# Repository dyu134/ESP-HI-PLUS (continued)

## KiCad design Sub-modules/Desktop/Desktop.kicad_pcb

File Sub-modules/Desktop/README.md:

# Desktop Sub-module

The **Desktop** sub-module is an environment-sensing and time-keeping expansion board for the **ESP-HI-PLUS**. It transforms the voice assistant into a desktop companion capable of monitoring room conditions and detecting human presence.

## Features

### Core Compute

- **RP2040** (U3) — Dual-core ARM Cortex-M0+ microcontroller to handle local sensor processing and timing.
- **16 Mbit Flash** (U1) — Storage for RP2040 firmware.

### Environment Sensors

- **SHT4x** (U5) — High-accuracy relative humidity and temperature sensor.
- **STHS34PF80** (U6) — Infrared sensor for presence and motion detection.
- **VEML7700** (U7) — Ambient light sensor for automatic display brightness adjustment.

### Time Keeping

- **MCP79410** (U8) — I²C Real-Time Clock with SRAM and battery backup.
- **CR2032 Battery** (BT1) — Ensures the clock keeps time even when the main board is powered off.

### Identification & Metadata

The Desktop module follows the standard [ESP-HI-PLUS identification protocol](../README.md).

- **R_ID (383 kΩ)** — Identifies the module as **Class 3 (Sensor — Environmental)**.
- **AT24CS02** (U10) — 2 Kbit I²C EEPROM carrying module metadata and serial number.

#### EEPROM Metadata

| Offset | Size | Field | Value (Hex) | Value (Decoded) | Description |
| :------: | :----: | :------ | :-----------: | :---------------- | :------------ |
| 0x00 | 4 | Magic Number | 45 53 50 4D | "ESPM" | ASCII sanity check |
| 0x04 | 1 | Class ID | 0x03 | 3 | Sensor - Environmental |
| 0x05 | 1 | Module ID | 0x01 | 1 | Desktop v1.17 |
| 0x06 | 1 | HW Revision | 0x01 | 1 | First PCB revision |
| 0x07 | 2 | FW Revision | 0x1101 | 1.17 | Major.Minor |
| 0x09 | 1 | Protocol Revision | 0x01 | 1 | Communication protocol v1 |
| 0x0A | 1 | Power Requirement | 0x00 | Self-powered | USB-C powered, no V_BUS needed |
| 0x0B | 2 | Max Current (mA) | 0x01F4 | 500 mA | Maximum draw (little-endian) |
| 0x0D | 2 | Min Voltage (mV) | 0x1194 | 4500 mV | Minimum supply voltage (little-endian) |
| 0x0F | 2 | Boot Delay (ms) | 0x0064 | 100 ms | Power-on delay (little-endian) |
| 0x11 | 4 | Capability Bitmask | 0x0000000D | — | Bits 0, 2, 3 enabled (see below) |
| 0x15 | 16 | Module Name | 44 65 73 6B... | "Desktop" | ASCII, null-terminated |
| 0x25 | 16 | Serial Number | 44 43 2D 30... | "DC-001-ABCD" | ASCII, null-terminated |
| 0x35 | 198 | User Data | — | — | Available for custom data |
| 0xFB | 4 | CRC32 | 0xXXXXXXXX | — | CRC32 of bytes 0x00–0xFA |

#### Capability Bitmask

**Value:** `0x0000000D` (Bits 0, 2, and 3 set)

| Bit | Value | Capability | Status |
| :---: | :---: | :--- | :--- |
| 0 | 0x01 | Needs Calibration | ✅ Enabled |
| 1 | 0x02 | Requires ACK | ❌ Disabled |
| 2 | 0x04 | Async Data | ✅ Enabled |
| 3 | 0x08 | Supports Sleep | ✅ Enabled |
| 4 | 0x10 | Has Emergency Stop | ❌ Disabled |
| 5 | 0x20 | Supports OTA | ❌ Disabled |
| 6 | 0x40 | Has Battery Backup | ❌ Disabled |
| 7 | 0x80 | Requires Bootloader Mode | ❌ Disabled |
| 8–31 | — | Reserved | — |

### User Interface & IO

- **WS2812B-2020** (D2) — Addressable RGB LED for status or mood lighting.
- **Tactile Switches** (SW1, SW3) — Reset and bootmode selection switching.
- **Snooze Button** (SW2) — **Kailh MX mechanical keyboard switch** (hotswap) for sleep mode activation.
- **USB-C Port** (J1) — For independent programming and powering of the RP2040.

## Integration

This module identifies itself as an environmental sensor class. The ESP-HI-PLUS main board can read data from the onboard sensors through commands to the RP2040 via UART through the magnetic pogo-pin connectors.

### Pinouts (Magnetic Pogo Connectors)

The Desktop module uses two 5-pin magnetic pogo-pin connectors to interface with the main board.

#### J2 (MAG1)

| Pin | Name   | Description                                           |
| --- | ------ | ----------------------------------------------------- |
| 1   | VMAIN  | 2-way power bus shared with main module               |
| 2   | GND    | Ground                                                |
| 3   | UART RX| From main module for data transmission                |
| 4   | UART TX| From main module for data transmission                |
| 5   | EN     | Main module control to enable/disable submodule power |

#### J3 (MAG2)

| Pin | Name     | Description                                     |
| --- | -------- | ----------------------------------------------- |
| 1   | I2C SDA  | For reading module ID metadata EEPROM           |
| 2   | I2C SCL  | For reading module ID metadata EEPROM           |
| 3   | AUX1/ID0 | Hardware class identifier resistor              |
| 4   | AUX2     | Auxiliary data pin (unused)                     |
| 5   | AUX3     | Auxiliary data pin (unused)                     |

## Repository Layout

```text
.
├── Desktop.kicad_pro           # KiCad project file
├── Desktop.kicad_sch           # Schematic
├── Desktop.kicad_pcb           # PCB layout
├── Desktop Symbols/            # Project-local schematic symbols
├── Desktop Footprints/         # Project-local footprint libraries
├── Desktop 3D Models/          # STEP models
└── production/                 # Manufacturing outputs
    ├── bom.csv                 # Bill of materials
    └── ESP-HI-PLUS_Desktop_Sub-module_v1.17.zip # Production archive (latest)
```

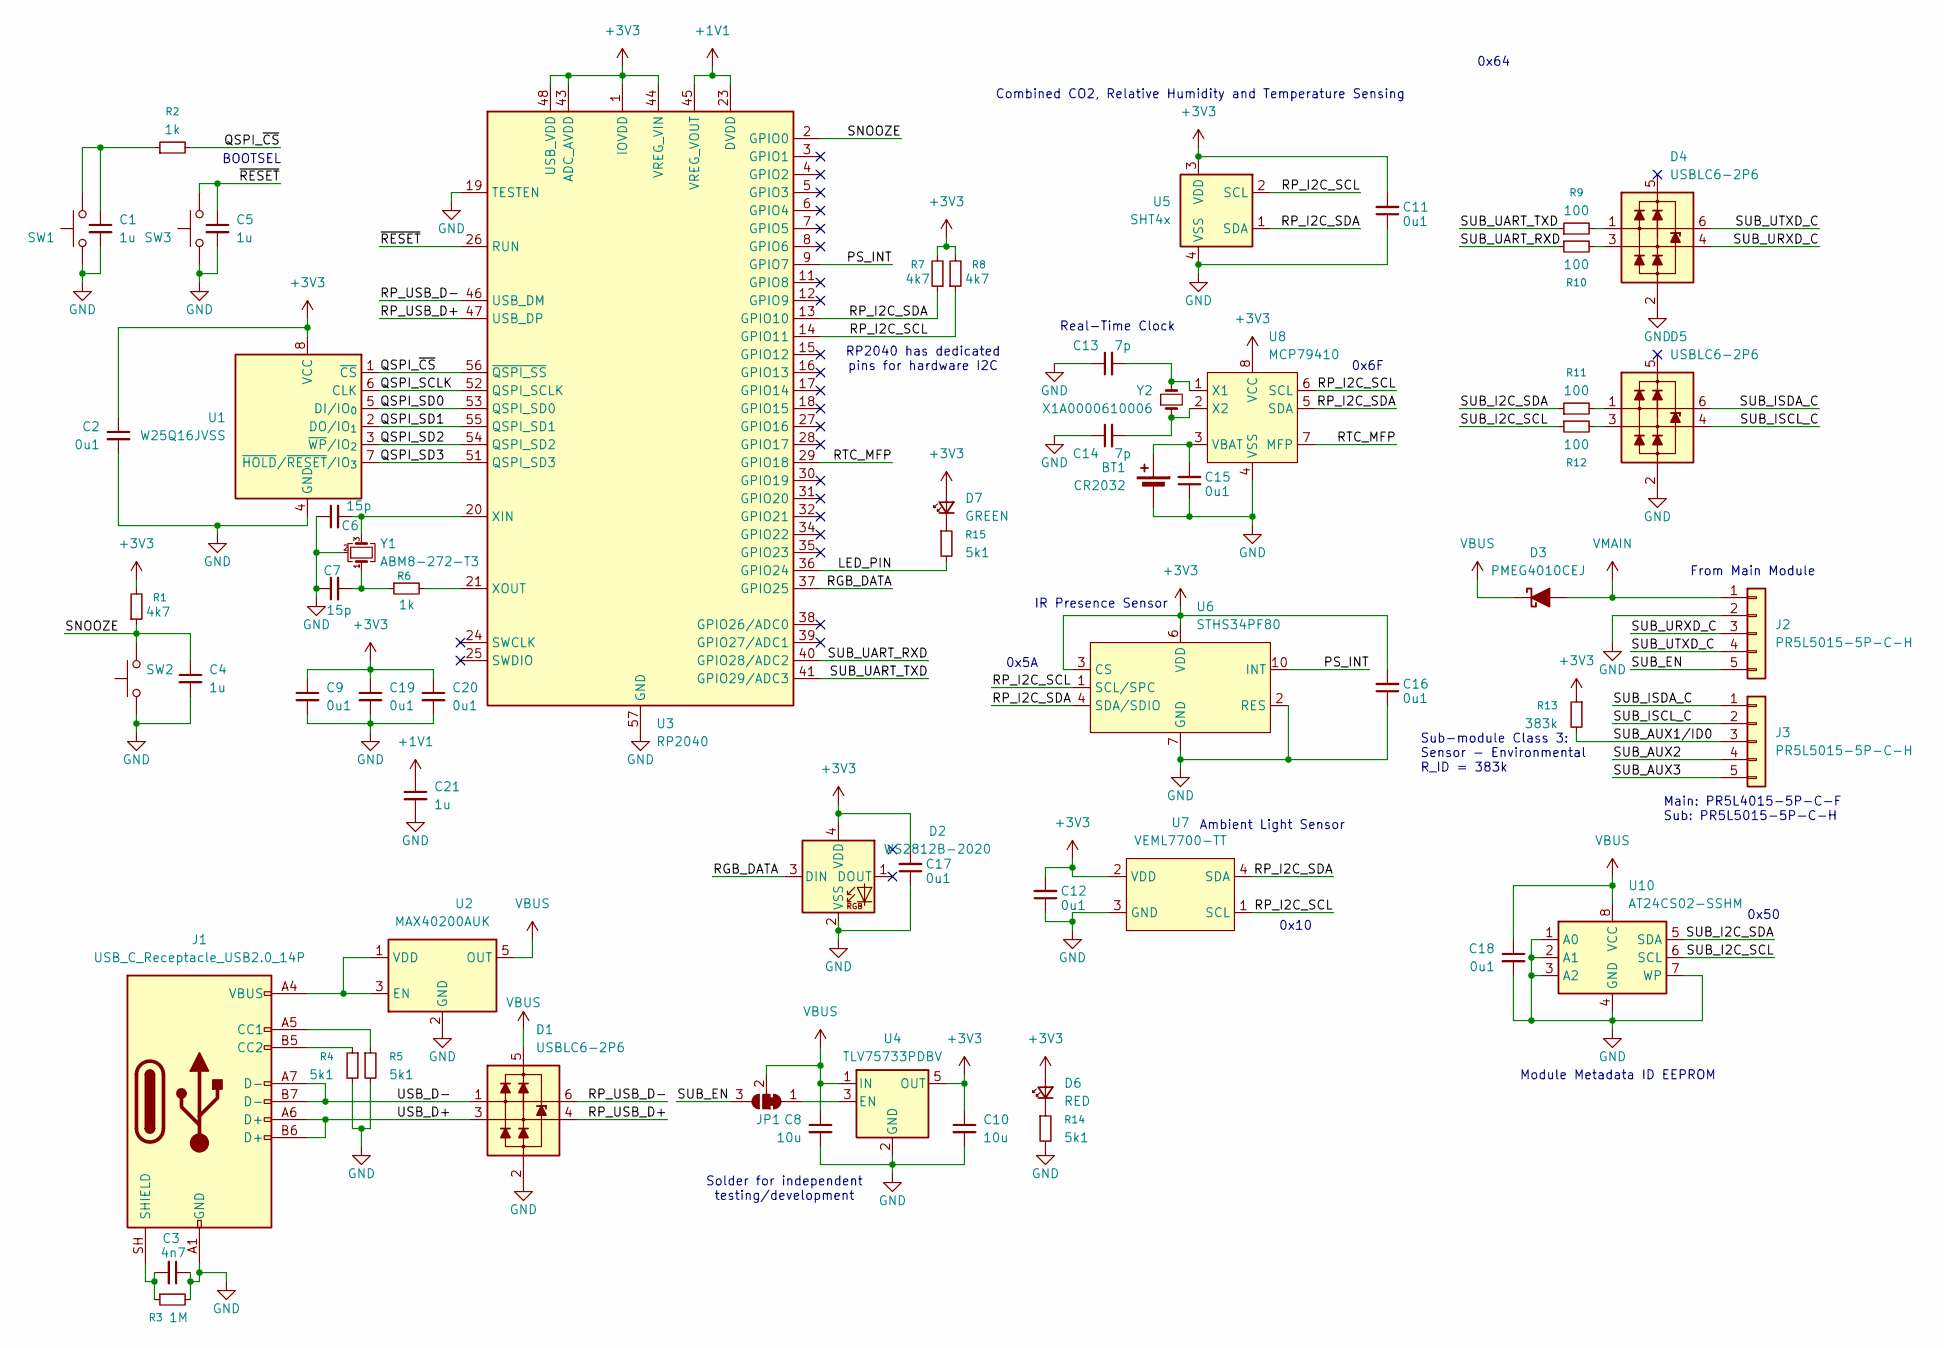
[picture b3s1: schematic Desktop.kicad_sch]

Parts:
BT1: CR2032; BatteryHolder_Keystone_1060_1x2032
C1, C4, C5, C21: 1u; C_0402_1005Metric
C2, C9, C11, C12, C15, C16, C17, C18, C19, C20: 0u1; C_0402_1005Metric
C3: 4n7; C_0402_1005Metric
C6, C7: 15p; C_0402_1005Metric
C8, C10: 10u; C_0402_1005Metric
C13, C14: 7p; C_0402_1005Metric
D1, D4, D5: USBLC6-2P6; SOT-666
D2: WS2812B-2020; LED_WS2812B-2020_PLCC4_2.0x2.0mm
D3: PMEG4010CEJ; D_SOD-323F
D6: RED; LED_0805_2012Metric
D7: GREEN; LED_0805_2012Metric
J1: USB_C_Receptacle_USB2.0_14P; USB_C_Receptacle_HCTL_HC-TYPE-C-16P-01A
J2, J3: PR5L5015-5P-C-H; PinHeader_1x05_P2.54mm_Vertical
JP1: SolderJumper_3_Bridged12; SolderJumper-3_P1.3mm_Bridged12_RoundedPad1.0x1.5mm
R1, R7, R8: 4k7; R_0402_1005Metric
R2, R6: 1k; R_0402_1005Metric
R3: 1M; R_0402_1005Metric
R4, R5, R14, R15: 5k1; R_0402_1005Metric
R9, R10, R11, R12: 100; R_0402_1005Metric
R13: 383k; R_0402_1005Metric
SW1, SW3: SKRPACE010; SW_Push_1P1T_NO_Vertical_Wuerth_434133025816
SW2: SW_Push; SW_Hotswap_Kailh_MX
U1: W25Q16JVSS; SOIC-8_5.3x5.3mm_P1.27mm
U2: MAX40200AUK; SOT-23-5
U3: RP2040; QFN-56-1EP_7x7mm_P0.4mm_EP3.2x3.2mm
U4: TLV75733PDBV; SOT-23-5
U5: SHT4x; Sensirion_DFN-4_1.5x1.5mm_P0.8mm_SHT4x_NoCentralPad
U6: STHS34PF80; XDCR_STHS34PF80TR
U7: VEML7700-TT
U8: MCP79410; SOIC-8_3.9x4.9mm_P1.27mm
U10: AT24CS02-SSHM; SOIC-8_3.9x4.9mm_P1.27mm
Y1: ABM8-272-T3; Crystal_SMD_3225-4Pin_3.2x2.5mm
Y2: X1A0000610006; Crystal_SMD_2012-2Pin_2.0x1.2mm

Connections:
+1V1: C21.1, U3.23 (DVDD), U3.45 (VREG_VOUT), U3.50 (DVDD)
+3V3: C2.1, C9.1, C10.1, C11.2, C12.2, C16.2, C17.2, C19.1, C20.1, D2.4 (VDD), D6.2 (A), D7.2 (A), R1.2, R7.2, R8.2, R13.1, U1.8 (VCC), U3.1 (IOVDD), U3.10 (IOVDD), U3.22 (IOVDD), U3.33 (IOVDD), U3.42 (IOVDD), U3.43 (ADC_AVDD), U3.44 (VREG_VIN), U3.48 (USB_VDD), U3.49 (IOVDD), U4.5 (OUT), U5.3 (VDD), U6.3 (CS), U6.6 (VDD), U6.9 (VDD), U7.2 (VDD), U8.8 (VCC)
/LED_PIN: R15.2, U3.36 (GPIO24)
/PS_INT: U3.9 (GPIO7), U6.10 (INT)
/QSPI_SCLK: U1.6 (CLK), U3.52 (QSPI_SCLK)
/QSPI_SD0: U1.5 (DI/IO_{0}), U3.53 (QSPI_SD0)
/QSPI_SD1: U1.2 (DO/IO_{1}), U3.55 (QSPI_SD1)
/QSPI_SD2: U1.3 (~WP/IO_{2}), U3.54 (QSPI_SD2)
/QSPI_SD3: U1.7 (~HOLD/~RESET/IO_{3}), U3.51 (QSPI_SD3)
/QSPI_~CS: R2.2, U1.1 (~CS), U3.56 (~QSPI_SS)
/RGB_DATA: D2.3 (DIN), U3.37 (GPIO25)
/RP_I2C_SCL: R8.1, U3.14 (GPIO11), U5.2 (SCL), U6.1 (SCL/SPC), U7.1 (SCL), U8.6 (SCL)
/RP_I2C_SDA: R7.1, U3.13 (GPIO10), U5.1 (SDA), U6.4 (SDA/SDIO), U7.4 (SDA), U8.5 (SDA)
/RP_USB_D+: D1.4 (L2), U3.47 (USB_DP)
/RP_USB_D-: D1.6 (L1), U3.46 (USB_DM)
/RTC_MFP: U3.29 (GPIO18), U8.7 (MFP)
/SNOOZE: C4.1, R1.1, SW2.2, U3.2 (GPIO0)
/SUB_AUX1/ID0: J3.3, R13.2
/SUB_AUX2: J3.4
/SUB_AUX3: J3.5
/SUB_EN: J2.5, JP1.3 (B)
/SUB_I2C_SCL: R12.1, U10.6 (SCL)
/SUB_I2C_SDA: R11.1, U10.5 (SDA)
/SUB_ISCL_C: D5.4 (L2), J3.2
/SUB_ISDA_C: D5.6 (L1), J3.1
/SUB_UART_RXD: R10.1, U3.40 (GPIO28/ADC2)
/SUB_UART_TXD: R9.1, U3.41 (GPIO29/ADC3)
/SUB_URXD_C: D4.4 (L2), J2.3
/SUB_UTXD_C: D4.6 (L1), J2.4
/USB_D+: D1.3 (L2), J1.A6 (D+), J1.B6 (D+)
/USB_D-: D1.1 (L1), J1.A7 (D-), J1.B7 (D-)
/~RESET: C5.1, SW3.2, U3.26 (RUN)
GND: BT1.2 (-), C1.2, C2.2, C3.1, C4.2, C5.2, C6.1, C7.1, C8.2, C9.2, C10.2, C11.1, C12.1, C13.1, C14.1, C15.1, C16.1, C17.1, C18.2, C19.2, C20.2, C21.2, D1.2 (VN), D2.2 (VSS), D4.2 (VN), D5.2 (VN), J1.A1 (GND), J1.A12 (GND), J1.B1 (GND), J1.B12 (GND), J2.2, R3.2, R4.2, R5.2, R14.2, SW1.1, SW2.1, SW3.1, U1.4 (GND), U2.2 (GND), U3.19 (TESTEN), U3.57 (GND), U4.2 (GND), U5.4 (VSS), U6.2 (RES), U6.7 (GND), U6.8 (GND), U7.3 (GND), U8.4 (VSS), U10.1 (A0), U10.2 (A1), U10.3 (A2), U10.4 (GND), U10.7 (WP), Y1.2 (G), Y1.4 (G)
unnamed: BT1.1 (+), C15.2, U8.3 (VBAT)
unnamed: C1.1, R2.1, SW1.2
unnamed: C7.2, R6.1, Y1.1
unnamed: D4.1 (L1), R9.2
unnamed: D4.3 (L2), R10.2
unnamed: D5.1 (L1), R11.2
unnamed: D5.3 (L2), R12.2
unnamed: D6.1 (K), R14.1
unnamed: D7.1 (K), R15.1
unnamed: J1.A5 (CC1), R5.1
unnamed: J1.B5 (CC2), R4.1
unnamed: C3.2, J1.SH (SHIELD), R3.1
unnamed: JP1.1 (A), U4.3 (EN)
unnamed: J1.A4 (VBUS), J1.A9 (VBUS), J1.B4 (VBUS), J1.B9 (VBUS), U2.1 (VDD), U2.3 (EN)
unnamed: C6.2, U3.20 (XIN), Y1.3
unnamed: R6.2, U3.21 (XOUT)
unnamed: C13.2, U8.1 (X1), Y2.2
unnamed: C14.2, U8.2 (X2), Y2.1
VBUS: C8.1, C18.1, D1.5 (VP), D3.1 (K), JP1.2 (C), U2.5 (OUT), U4.1 (IN), U10.8 (VCC)
VMAIN: D3.2 (A), J2.1

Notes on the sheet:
0x64
Ambient Light Sensor
Real-Time Clock
0x5A
IR Presence Sensor
Solder for independent testing/development
Combined CO2, Relative Humidity and Temperature Sensing
0x10
From Main Module
Sub-module Class 3: Sensor - Environmental R_ID = 383k
0x50
Module Metadata ID EEPROM
Main: PR5L4015-5P-C-F Sub: PR5L5015-5P-C-H
0x6F
BOOTSEL
RP2040 has dedicated pins for hardware I2C

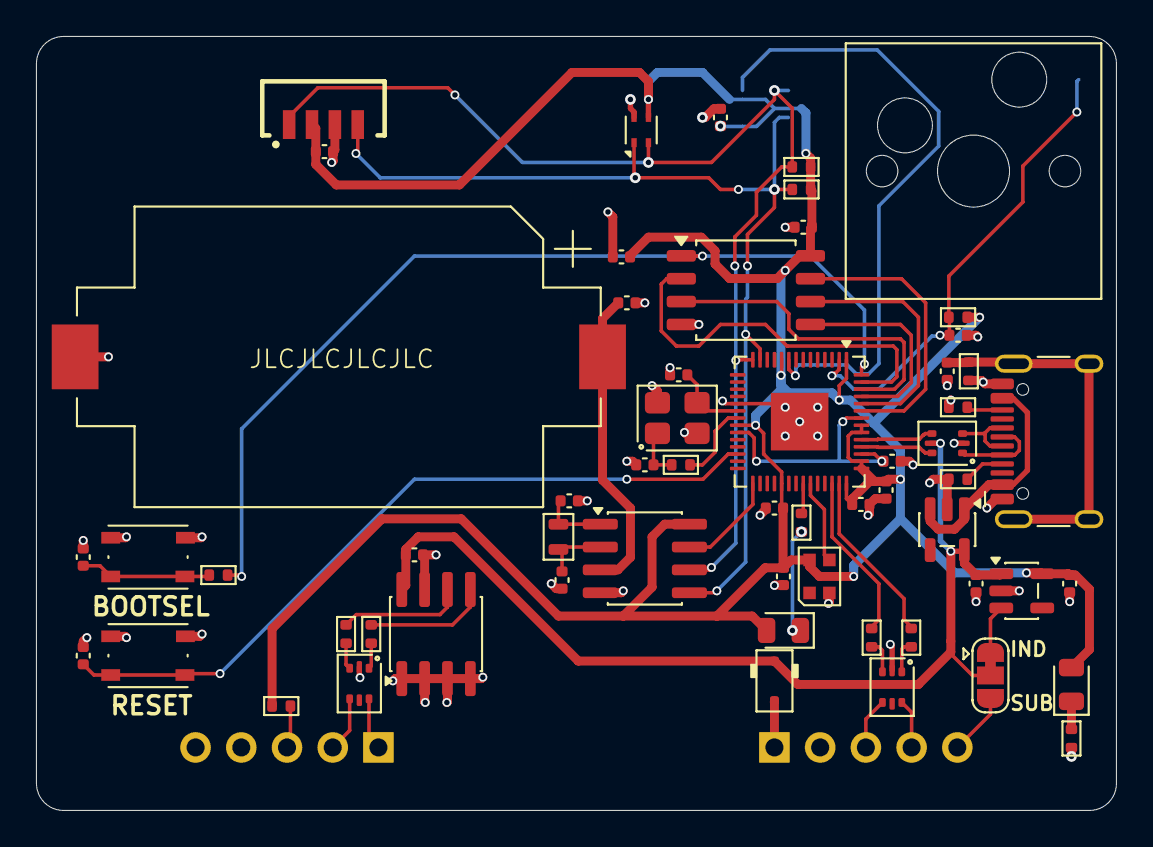
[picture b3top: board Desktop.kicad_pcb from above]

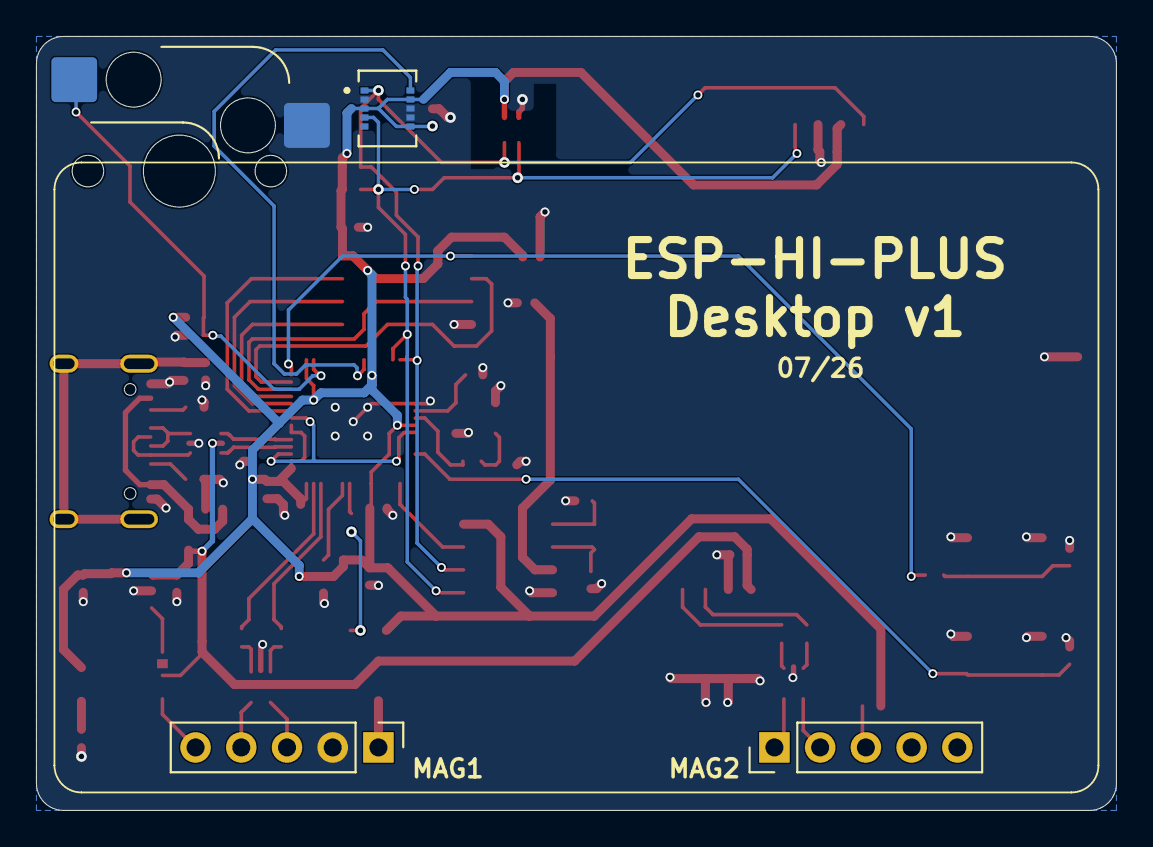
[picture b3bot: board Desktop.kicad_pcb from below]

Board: 2 copper layers, 60.0 x 43.0 mm, 62 parts (3 on the bottom side), 51 nets.

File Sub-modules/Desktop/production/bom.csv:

Designator,Footprint,Quantity,Value,LCSC Part #
BT1,BatteryHolder_Keystone_1060_1x2032,1,CR2032,
"C1, C21, C4, C5",0402,4,1u,
"C10, C8",0402,2,10u,
"C11, C12, C15, C16, C17, C18, C19, C2, C20, C9",0402,10,0u1,
"C13, C14",0402,2,7p,
C3,0402,1,4n7,
"C6, C7",0402,2,15p,
"D1, D4, D5",SOT-666,3,USBLC6-2P6,
D2,LED_WS2812B-2020_PLCC4_2.0x2.0mm,1,WS2812B-2020,
D3,D_SOD-323F,1,PMEG4010CEJ,
D6,0805,1,RED,
D7,0805,1,GREEN,
J1,USB_C_Receptacle_HCTL_HC-TYPE-C-16P-01A,1,USB_C_Receptacle_USB2.0_14P,
"J2, J3",PinHeader_1x05_P2.54mm_Vertical,2,PR5L5015-5P-C-H,
"R1, R7, R8",0402,3,4k7,
"R10, R11, R12, R9",0402,4,100,
R13,0402,1,383k,
"R14, R15, R4, R5",0402,4,5k1,
"R2, R6",0402,2,1k,
R3,0402,1,1M,
"SW1, SW3",SW_Push_1P1T_NO_Vertical_Wuerth_434133025816,2,SKRPACE010,
SW2,SW_Hotswap_Kailh_MX,1,SW_Push,
U1,SOIC-8_5.3x5.3mm_P1.27mm,1,W25Q16JVSS,
U10,SOIC-8_3.9x4.9mm_P1.27mm,1,AT24CS02-SSHM,
U2,SOT-23-5,1,MAX40200AUK,
U3,QFN-56-1EP_7x7mm_P0.4mm_EP3.2x3.2mm,1,RP2040,
U4,SOT-23-5,1,TLV75733PDBV,
U5,Sensirion_DFN-4_1.5x1.5mm_P0.8mm_SHT4x_NoCentralPad,1,SHT4x,
U6,XDCR_STHS34PF80TR,1,STHS34PF80,
U7,VEML7700-TT,1,VEML7700-TT,
U8,SOIC-8_3.9x4.9mm_P1.27mm,1,MCP79410,
Y1,Crystal_SMD_3225-4Pin_3.2x2.5mm,1,ABM8-272-T3,
Y2,Crystal_SMD_2012-2Pin_2.0x1.2mm,1,X1A0000610006,
